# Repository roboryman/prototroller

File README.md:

## About
The Prototroller is a ***modular*** controller that is full-stack, feature-rich, responsive, and robust. The controller could be used for any HID-compliant purpose, but we focus on developing hot-swappable modules that can form customizable gamepads.

A potential use case is general hardware level remapping for quality of life. Another is rapidly prototyping different controller layouts for games or simulations in development.

Our team consists of 5 members:
- Yu-yang Hsieh
- Britton McLeavy
- Caleb O'Malley
- Merrick Ryman
- Evan Zhang

This project is developed in conjunction with the UF CpE Capstone program (Fall 2022 - Spring 2023). This project is self-funded. As such, donations are appreciated in this educational pursuit (hardware is not cheap nowadays).

## Architecture and Aesthetics
At the highest abstraction the Prototroller consists of the following:
- Master Board 
- Module Boards
- Component Interfaces
- Enclosures
- Firmware

### Master Board

<p>

The master board handles the data store of connected modules, transfers and receives data with modules over SPI, transfers and receives HID data over USB with the host, rescans modules, has buttons for various functions, etc. Most of the master board also serves as the the 4x5 grid of module slots the user can snap modules to using magnetic pogo-pin connectors.

<br clear="left"/>
</p>

The master board has buttons for rescanning, resetting, and flashing. There are header pins for interfacing with haptic feedback motors. A 3-pin JST-SH header (1.00mm) is available for serial wire debug. There is a USB-C receptacle (2.0) for power and data connection with the host.

The connection interface between the master board and module boards uses 6-pin magnetic pogo-pin connectors. These carry VCC, GND, and SPI signals, while maintaining a solid physical connection. The master board feeds modules with 3.3V.

### Module Boards

<p>

Module boards are generic and constrained at 30x30mm with no direct user interface (except for the connector and SWD headers). On the sides are headers providing 14 signals to a component interface board that would sit above. This way there are no unique module boards for each component, and we simply offload the task to the component interface board by hand.
<br clear="right"/>
</p>

### Component Interface Boards

<p>

The component interface boards are veroboards sitting above the module board headers. We may freely route signals from the module board to a component, the direct user interface.
<br clear="left"/>
</p>

### Enclosures

This would not be a very comfortable controller to use without enclosures.

The master board is enclosed by a chassis and grips. The master board is screwed to the chassis.

The module enclosures contain the module board and component interface boards, but do not cover the component.

### Firmware

Each type of module has its own assosciated firmware that can be flashed via the SWD header pins with picoprobe firmware. The master board can be flashed via the normal way of "dragging" the binaries. See below for more details on flashing. The Prototroller has been extensively tested on Windows systems, but will likely work on Mac, Linux, and generally any OS that supports HID gamepads.

## Usage
There are a few ways you may use the Prototroller.
### _Our Hardware, Our Software_
Recommended. This combines our hardware listed above with the firmware to do the job.
The end result is a full-stack modular controller.

Our recommended PCB supplier is JLCPCB, and we are working on formalizing our recommendations for ordering.

### _Your Hardware, Our Software_
If you want to develop your own hardware to use with our software, that is excellent! In fact, we are curious to see your designs.

You may use our designs as a starting point. For example, you may want to make the modules slightly larger.

## Building and Flashing Master Boards
You may use the provided VSCode launch debug configuration and flash task. This requires a Picoprobe, OpenOCD, and Cortex Debug. Instructions are available in ```/ide```.
An easier way is to use the USB receptacle to mount and flash RP2040 binaries (.uf2), accessible by holding down BOOTSEL and performing a reset. **If you are using VSCode, you can simply edit settings.json for your SDK path, build the target, and proceed to step 5**. Otherwise, the process to generate the binary is as so:
1. Ensure you have the Pico SDK cloned somewhere, such as ```~/pico-sdk```.
2. Make and cd into a 'build' subdirectory, and export the Pico SDK path:
    ```
    $ cd prototroller
    $ mkdir build
    $ cd build
    $ export PICO_SDK_PATH=...
    ```
3. Generate the build targets:
    ```
    $ cmake -DPICO_BOARD=prototroller ..
    ```
4. Build all targets by running `make`. To build only host, master, or module targets, cd into the respective directory (generated by the cmake command above) and execute `make`. In this case, you can just `cd` into master and execute `make`.
5. This will generate the appropriate `.uf2` binaries, which can be flashed by dragging onto the mount.

## Building and Flashing Module Boards
The module boards do not have a USB receptacle. You must use SWD in conjunction with a debug probe. We recommend the official Raspberry Pi Debug Probe ($12), or a Pico flashed with the Picoprobe firmware.

Instructions are available in ```/ide```. This is how you might do it after setting up Picoprobe, OpenOCD, etc:
1. Follow the steps listed in "Building and Flashing Master Boards" to generate the binary for the module boards.
2. Connect SWDIO and SWCLK from debug probe to the SWD headers above the flash on the module board (labeled on rear silkscreen).
3. Connect a *common ground* between the Picoprobe and the module board.
4. Snap the module board to a powered master board (alternatively, supply 3V3 through the female header).
5. If you are using WSL, pass-through the Picoprobe in Powershell using ```usbipd```.
6. Use the '```Prototroller Flash```' task in VSCode, or execute the following command, where `joystick-module.elf` is the name of the ELF executable generated previously:
    ```
    sudo openocd -f interface/cmsis-dap.cfg -f target/rp2040.cfg -c "adapter speed 5000" -c "program build/module/joystick-module.elf verify reset exit"
    ```
If all went well, the module board should be flashed. You can safely remove the SWD wires and set the debug probe aside.

Documentation for the official Raspberry Pi Debug Probe:
https://www.raspberrypi.com/documentation/microcontrollers/debug-probe.html

Alternatively, here is an excellent tutorial to setting up and using Picoprobe if you have a Pico available: https://github.com/robotdad/piconotes

## Roadmap
- [x] Proof of Concept Build
- [x] Basic Master/Module Firmware
- [x] Basic Host HID Drivers
- [x] Basic Component Support
- [x] Prototype Build
- [x] Interconnect Design
- [x] Module Board Design(s)
- [x] Master Board Design
- [x] Chassis/Module Enclosure Designs
- [x] Advanced Firmware
- [x] Advanced HID Drivers
- [x] Advanced Component Support
- [x] Finalized Firmware
- [x] Prototroller Artifact
- [ ] Stretch: Wireless Support
- [ ] Stretch: Power Optimization
- [ ] Stretch: More types of modules

Ideas for future modules: Trigger, D-Pad, Accelerometer, Gyroscope, Rounded Buttons. Could also do some cool things non-gaming related, such as an IR blaster and Bluetooth TX/RX modules.
Adding new types of modules only requires the firmware and custom backpack.

## Acknowledgements
Thank you to our stakeholder Carsten Thue-Bludworth for his infinite wisdom. His assistance keeps the project grounded and evolving in the best way possible.

Thank you to Dr. Blanchard and the UF CpE Capstone program for direction and usage of lab space.

Thank you to the Raspberry Pi community for the hardware and software that made this project possible.

Thank you to Phil's Lab on YouTube for the excellent courses and tutorials on hardware design.

Thank you to user testing participants for valuable feedback. Their insights and suggestions have helped us refine our design and ensure that our final product meets the needs and expectations of its intended users.

Thank you to families, friends, and loved ones for their unwavering support and encouragement. Their belief in our abilities and commitment to our success has been a constant source of motivation and inspiration.

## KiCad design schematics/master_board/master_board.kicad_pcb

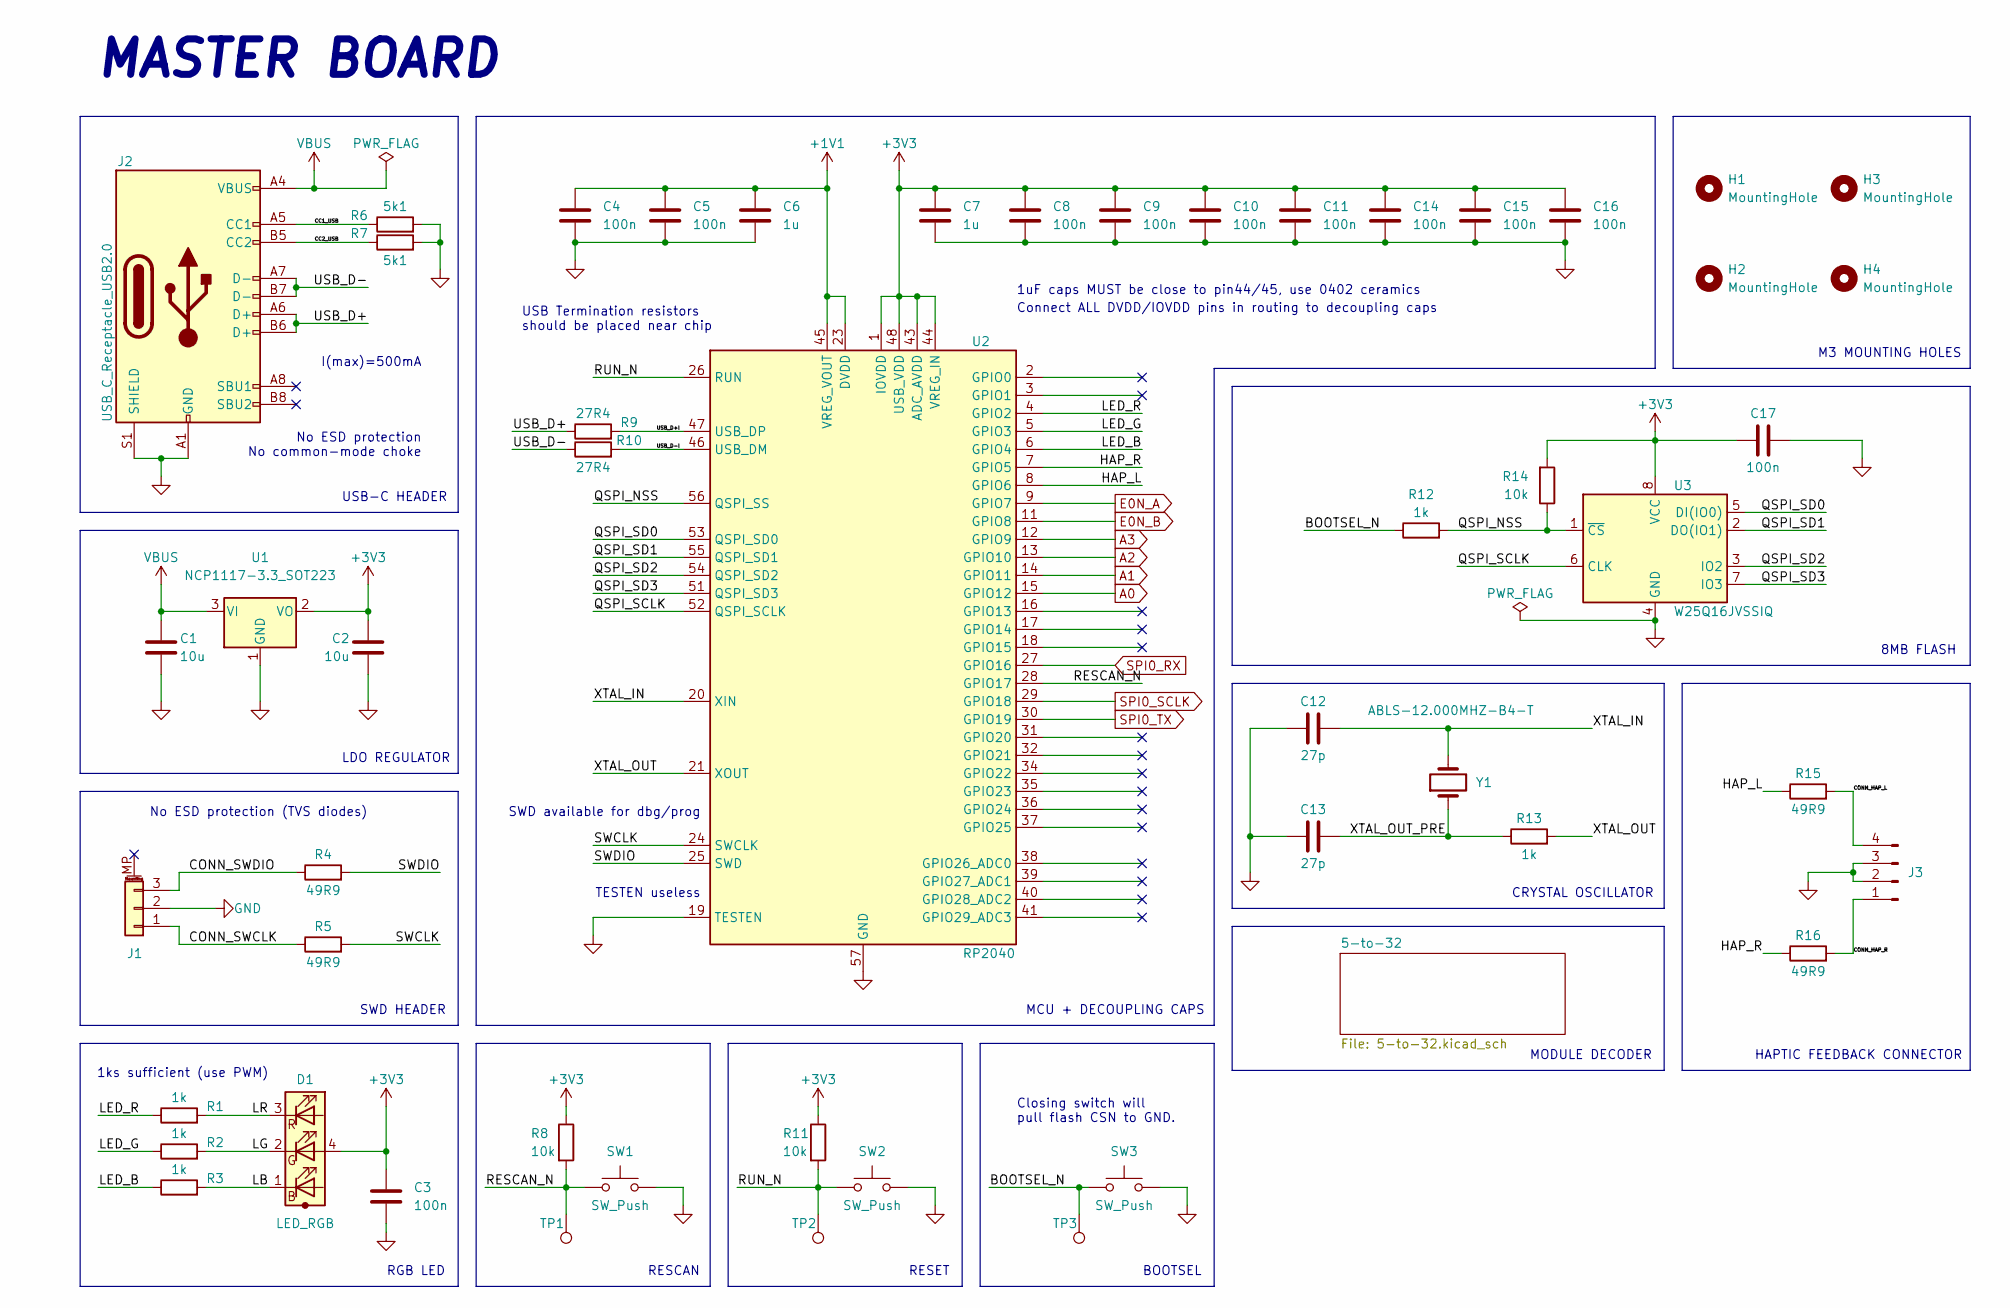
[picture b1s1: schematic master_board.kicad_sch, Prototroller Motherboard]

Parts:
C1, C2: 10u; C_0805_2012Metric; Manufacturer Part Number CL21A106KOQNNNG
C3, C4, C5, C8, C9, C10, C11, C14, C15, C16, C17: 100n; C_0402_1005Metric; Manufacturer Part Number C0402X7R100-104KNE-CT
C6, C7: 1u; C_0402_1005Metric; Manufacturer Part Number C0402X5R6R3-105KNP-CT
C12, C13: 27p; C_0402_1005Metric; Manufacturer Part Number C0402C0G250-270JNE-CT
D1: LED_RGB; LED_Cree-UHD111A; Manufacturer Part Number UHD111A-FKA-C3K23E1L3VG5ZB3Z3
H1, H2, H3, H4: MountingHole; MountingHole_3.2mm_M3
J1: Conn_01x03_MountingPin; JST_SH_BM03B-SRSS-TB_1x03-1MP_P1.00mm_Vertical
J2: USB_C_Receptacle_USB2.0; USB_C_Receptacle_GCT_USB4105-xx-A_16P_TopMnt_Horizontal; Manufacturer Part Number USB4105-GF-A
J3: Conn_01x04_Male; PinHeader_1x04_P2.54mm_Vertical
R1, R2, R3, R13: 1k; R_0402_1005Metric; Manufacturer Part Number RC0402FR-7W1KL
R4, R5: 49R9; R_0402_1005Metric; Manufacturer Part Number RC0402FR-7W49R9L
R6, R7: 5k1; R_0402_1005Metric; Manufacturer Part Number ERJ-2RKF5101X
R8, R11, R14: 10k; R_0402_1005Metric; Manufacturer Part Number RC0402JR-7W10KL
R9, R10: 27R4; R_0402_1005Metric; Manufacturer Part Number CRGP0402F27R
R12: 1k; R_0402_1005Metric; Manufacturer Part Number RC0402JR-7W10KL
R15, R16: 49R9; R_0402_1005Metric; Manufacturer Part Number RC0402FR-7W1KL
SW1, SW2, SW3: SW_Push; Switch_D6C40F1LFS; Manufacturer Part Number D6C40 F1 LFS
TP1, TP2, TP3: TestPoint; TestPoint_Pad_2.5x2.5mm
U1: NCP1117-3.3_SOT223; SOT-223-3_TabPin2; Manufacturer Part Number NCP1117LPST33T3G
U2: RP2040; QFN-56-1EP_7x7mm_P0.4mm_EP3.2x3.2mm; Manufacturer Part Number SC0914(13)
U3: W25Q16JVSSIQ; SOIC-8_5.23x5.23mm_P1.27mm; Manufacturer Part Number W25Q16JVSSIQ
Y1: ABLS-12.000MHZ-B4-T; XTAL_ABLS-12.000MHZ-B4-T; Manufacturer Part Number ABLS-12.000MHZ-B4-T

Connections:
+1V1: C4.1, C5.1, C6.1, U2.23 (DVDD), U2.45 (VREG_VOUT), U2.50 (DVDD)
+3V3: C2.2, C3.1, C7.1, C8.1, C9.1, C10.1, C11.1, C14.1, C15.1, C16.1, C17.1, D1.4 (A), R8.1, R11.1, R14.2, U1.2 (VO), U2.1 (IOVDD), U2.10 (IOVDD), U2.22 (IOVDD), U2.33 (IOVDD), U2.42 (IOVDD), U2.43 (ADC_AVDD), U2.44 (VREG_IN), U2.48 (USB_VDD), U2.49 (IOVDD), U3.8 (VCC); also elsewhere on the board
/BOOTSEL_N: R12.1, SW3.1, TP3.1
/CC1_USB: J2.A5 (CC1), R6.1
/CC2_USB: J2.B5 (CC2), R7.1
/CONN_HAP_L: J3.4, R15.2
/CONN_HAP_R: J3.1, R16.2
/CONN_SWCLK: J1.1, R5.1
/CONN_SWDIO: J1.3, R4.1
/HAP_L: R15.1, U2.8 (GPIO6)
/HAP_R: R16.1, U2.7 (GPIO5)
/LB: D1.1 (B), R3.2
/LED_B: R3.1, U2.6 (GPIO4)
/LED_G: R2.1, U2.5 (GPIO3)
/LED_R: R1.1, U2.4 (GPIO2)
/LG: D1.2 (G), R2.2
/LR: D1.3 (R), R1.2
/QSPI_NSS: R12.2, R14.1, U2.56 (QSPI_SS), U3.1 (~CS)
/QSPI_SCLK: U2.52 (QSPI_SCLK), U3.6 (CLK)
/QSPI_SD0: U2.53 (QSPI_SD0), U3.5 (DI(IO0))
/QSPI_SD1: U2.55 (QSPI_SD1), U3.2 (DO(IO1))
/QSPI_SD2: U2.54 (QSPI_SD2), U3.3 (IO2)
/QSPI_SD3: U2.51 (QSPI_SD3), U3.7 (IO3)
/RESCAN_N: R8.2, SW1.1, TP1.1, U2.28 (GPIO17)
/RUN_N: R11.2, SW2.1, TP2.1, U2.26 (RUN)
/SWCLK: R5.2, U2.24 (SWCLK)
/SWDIO: R4.2, U2.25 (SWD)
/USB_D+: J2.A6 (D+), J2.B6 (D+), R9.1
/USB_D+I: R9.2, U2.47 (USB_DP)
/USB_D-: J2.A7 (D-), J2.B7 (D-), R10.1
/USB_D-I: R10.2, U2.46 (USB_DM)
/XTAL_IN: C12.2, U2.20 (XIN), Y1.2
/XTAL_OUT: R13.2, U2.21 (XOUT)
/XTAL_OUT_PRE: C13.2, R13.1, Y1.1
A0: U2.15 (GPIO12); also elsewhere on the board
A1: U2.14 (GPIO11); also elsewhere on the board
A2: U2.13 (GPIO10); also elsewhere on the board
A3: U2.12 (GPIO9); also elsewhere on the board
E0N_A: U2.9 (GPIO7); also elsewhere on the board
E0N_B: U2.11 (GPIO8); also elsewhere on the board
GND: C1.2, C2.1, C3.2, C4.2, C5.2, C6.2, C7.2, C8.2, C9.2, C10.2, C11.2, C12.1, C13.1, C14.2, C15.2, C16.2, C17.2, J1.2, J2.A1 (GND), J2.A12 (GND), J2.B1 (GND), J2.B12 (GND), J2.S1 (SHIELD), J3.2, J3.3, R6.2, R7.2, SW1.2, SW2.2, SW3.2, U1.1 (GND), U2.19 (TESTEN), U2.57 (GND), U3.4 (GND); also elsewhere on the board
SPI0_RX: U2.27 (GPIO16); also elsewhere on the board
SPI0_SCLK: U2.29 (GPIO18); also elsewhere on the board
SPI0_TX: U2.30 (GPIO19); also elsewhere on the board
VBUS: C1.1, J2.A4 (VBUS), J2.A9 (VBUS), J2.B4 (VBUS), J2.B9 (VBUS), U1.3 (VI)

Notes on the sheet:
RESET
MODULE DECODER
SWD HEADER
1ks sufficient (use PWM)
USB-C HEADER
M3 MOUNTING HOLES
CRYSTAL OSCILLATOR
RGB LED
1uF caps MUST be close to pin44/45, use 0402 ceramics
USB Termination resistors should be placed near chip
TESTEN useless
HAPTIC FEEDBACK CONNECTOR
RESCAN
LDO REGULATOR
Connect ALL DVDD/IOVDD pins in routing to decoupling caps
No ESD protection No common-mode choke
SWD available for dbg/prog
BOOTSEL
8MB FLASH
Closing switch will pull flash CSN to GND.
I(max)=500mA
No ESD protection (TVS diodes)
MCU + DECOUPLING CAPS
MASTER BOARD

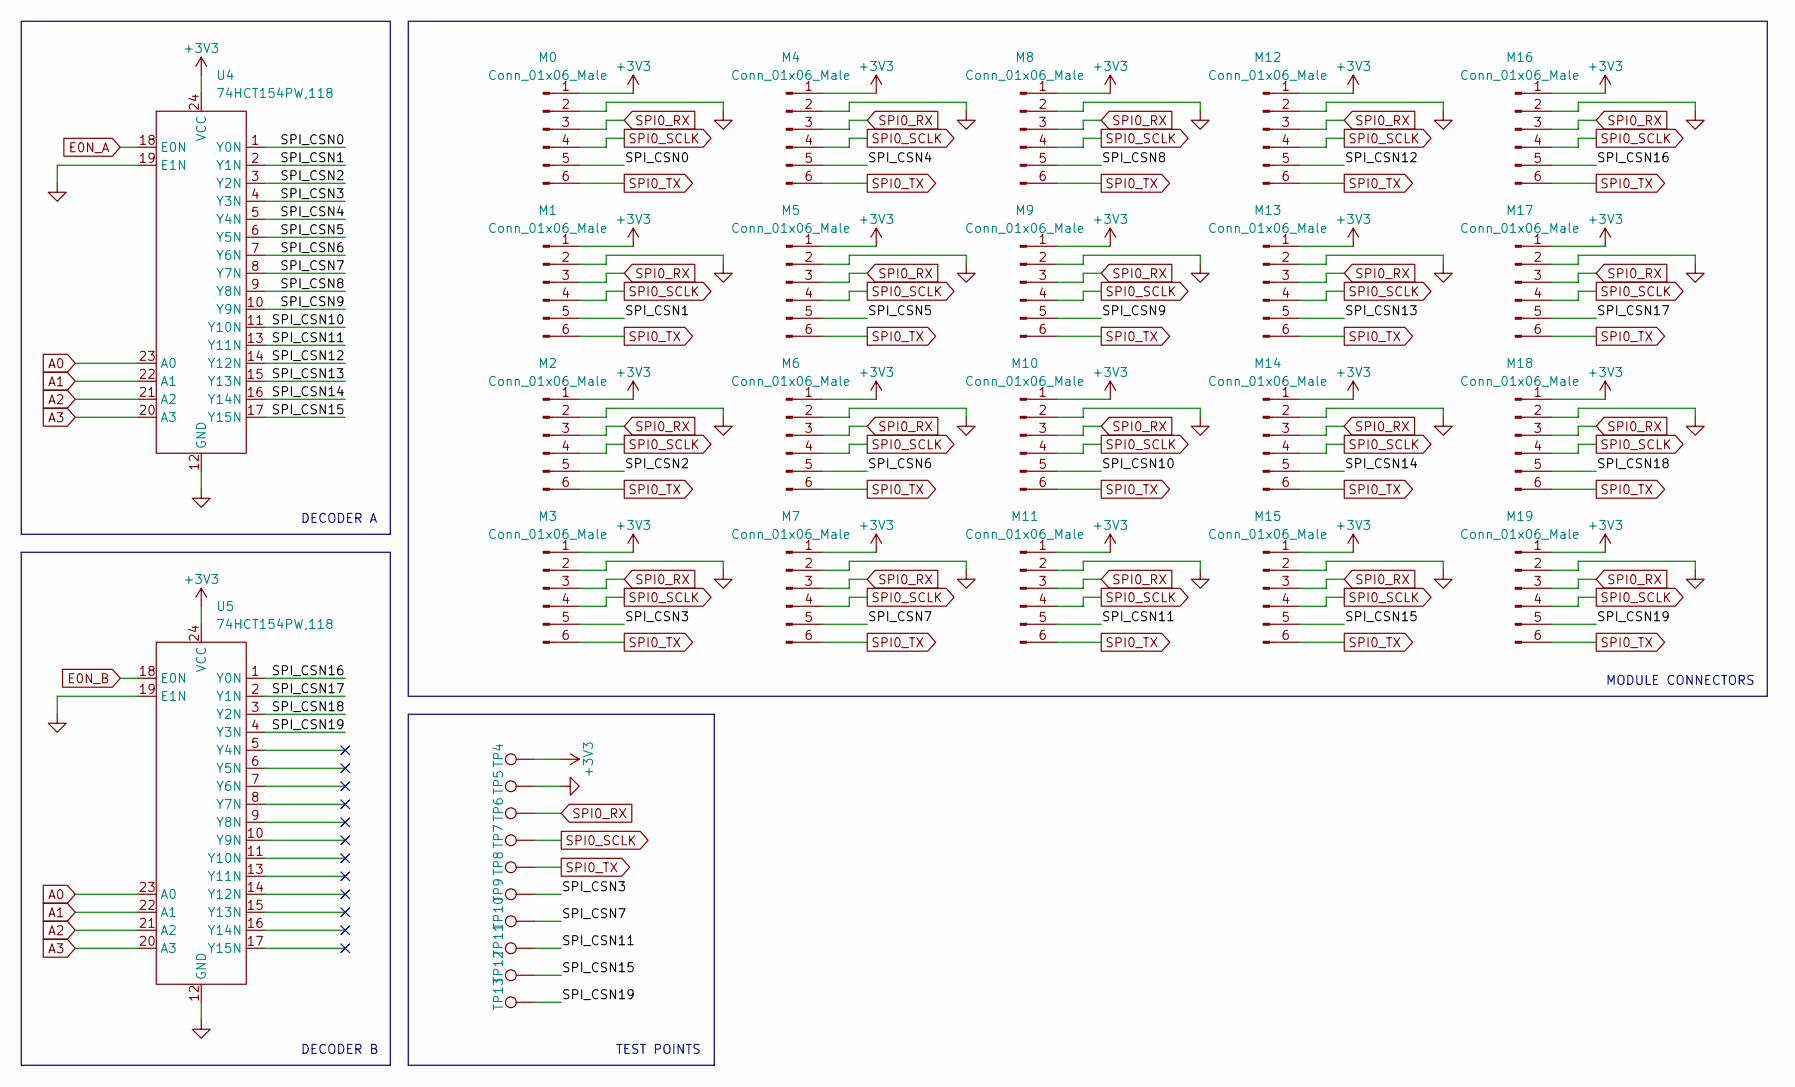
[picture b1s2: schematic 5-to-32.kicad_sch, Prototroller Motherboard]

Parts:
M0, M1, M2, M3, M4, M5, M6, M7, M8, M9, M10, M11, M12, M13, M14, M15, M16, M17, M18, M19: Conn_01x06_Male; Mag_Pogo_6P_P2.2mm_Female
TP4, TP5, TP6, TP7, TP8, TP9, TP10, TP11, TP12, TP13: TestPoint; TestPoint_Pad_2.5x2.5mm
U4, U5: 74HCT154PW,118; TSSOP-24_4.4x7.8mm_P0.65mm; Manufacturer Part Number 74HCT154PW,118

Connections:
+3V3: M0.1, M1.1, M2.1, M3.1, M4.1, M5.1, M6.1, M7.1, M8.1, M9.1, M10.1, M11.1, M12.1, M13.1, M14.1, M15.1, M16.1, M17.1, M18.1, M19.1, TP4.1, U4.24 (VCC), U5.24 (VCC); also elsewhere on the board
/5-to-32/SPI_CSN0: M0.5, U4.1 (Y0N)
/5-to-32/SPI_CSN1: M1.5, U4.2 (Y1N)
/5-to-32/SPI_CSN2: M2.5, U4.3 (Y2N)
/5-to-32/SPI_CSN3: M3.5, TP9.1, U4.4 (Y3N)
/5-to-32/SPI_CSN4: M4.5, U4.5 (Y4N)
/5-to-32/SPI_CSN5: M5.5, U4.6 (Y5N)
/5-to-32/SPI_CSN6: M6.5, U4.7 (Y6N)
/5-to-32/SPI_CSN7: M7.5, TP10.1, U4.8 (Y7N)
/5-to-32/SPI_CSN8: M8.5, U4.9 (Y8N)
/5-to-32/SPI_CSN9: M9.5, U4.10 (Y9N)
/5-to-32/SPI_CSN10: M10.5, U4.11 (Y10N)
/5-to-32/SPI_CSN11: M11.5, TP11.1, U4.13 (Y11N)
/5-to-32/SPI_CSN12: M12.5, U4.14 (Y12N)
/5-to-32/SPI_CSN13: M13.5, U4.15 (Y13N)
/5-to-32/SPI_CSN14: M14.5, U4.16 (Y14N)
/5-to-32/SPI_CSN15: M15.5, TP12.1, U4.17 (Y15N)
/5-to-32/SPI_CSN16: M16.5, U5.1 (Y0N)
/5-to-32/SPI_CSN17: M17.5, U5.2 (Y1N)
/5-to-32/SPI_CSN18: M18.5, U5.3 (Y2N)
/5-to-32/SPI_CSN19: M19.5, TP13.1, U5.4 (Y3N)
A0: U4.23 (A0), U5.23 (A0); also elsewhere on the board
A1: U4.22 (A1), U5.22 (A1); also elsewhere on the board
A2: U4.21 (A2), U5.21 (A2); also elsewhere on the board
A3: U4.20 (A3), U5.20 (A3); also elsewhere on the board
E0N_A: U4.18 (E0N); also elsewhere on the board
E0N_B: U5.18 (E0N); also elsewhere on the board
GND: M0.2, M1.2, M2.2, M3.2, M4.2, M5.2, M6.2, M7.2, M8.2, M9.2, M10.2, M11.2, M12.2, M13.2, M14.2, M15.2, M16.2, M17.2, M18.2, M19.2, TP5.1, U4.12 (GND), U4.19 (E1N), U5.12 (GND), U5.19 (E1N); also elsewhere on the board
SPI0_RX: M0.3, M1.3, M2.3, M3.3, M4.3, M5.3, M6.3, M7.3, M8.3, M9.3, M10.3, M11.3, M12.3, M13.3, M14.3, M15.3, M16.3, M17.3, M18.3, M19.3, TP6.1; also elsewhere on the board
SPI0_SCLK: M0.4, M1.4, M2.4, M3.4, M4.4, M5.4, M6.4, M7.4, M8.4, M9.4, M10.4, M11.4, M12.4, M13.4, M14.4, M15.4, M16.4, M17.4, M18.4, M19.4, TP7.1; also elsewhere on the board
SPI0_TX: M0.6, M1.6, M2.6, M3.6, M4.6, M5.6, M6.6, M7.6, M8.6, M9.6, M10.6, M11.6, M12.6, M13.6, M14.6, M15.6, M16.6, M17.6, M18.6, M19.6, TP8.1; also elsewhere on the board

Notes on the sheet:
MODULE CONNECTORS
DECODER B
DECODER A
TEST POINTS

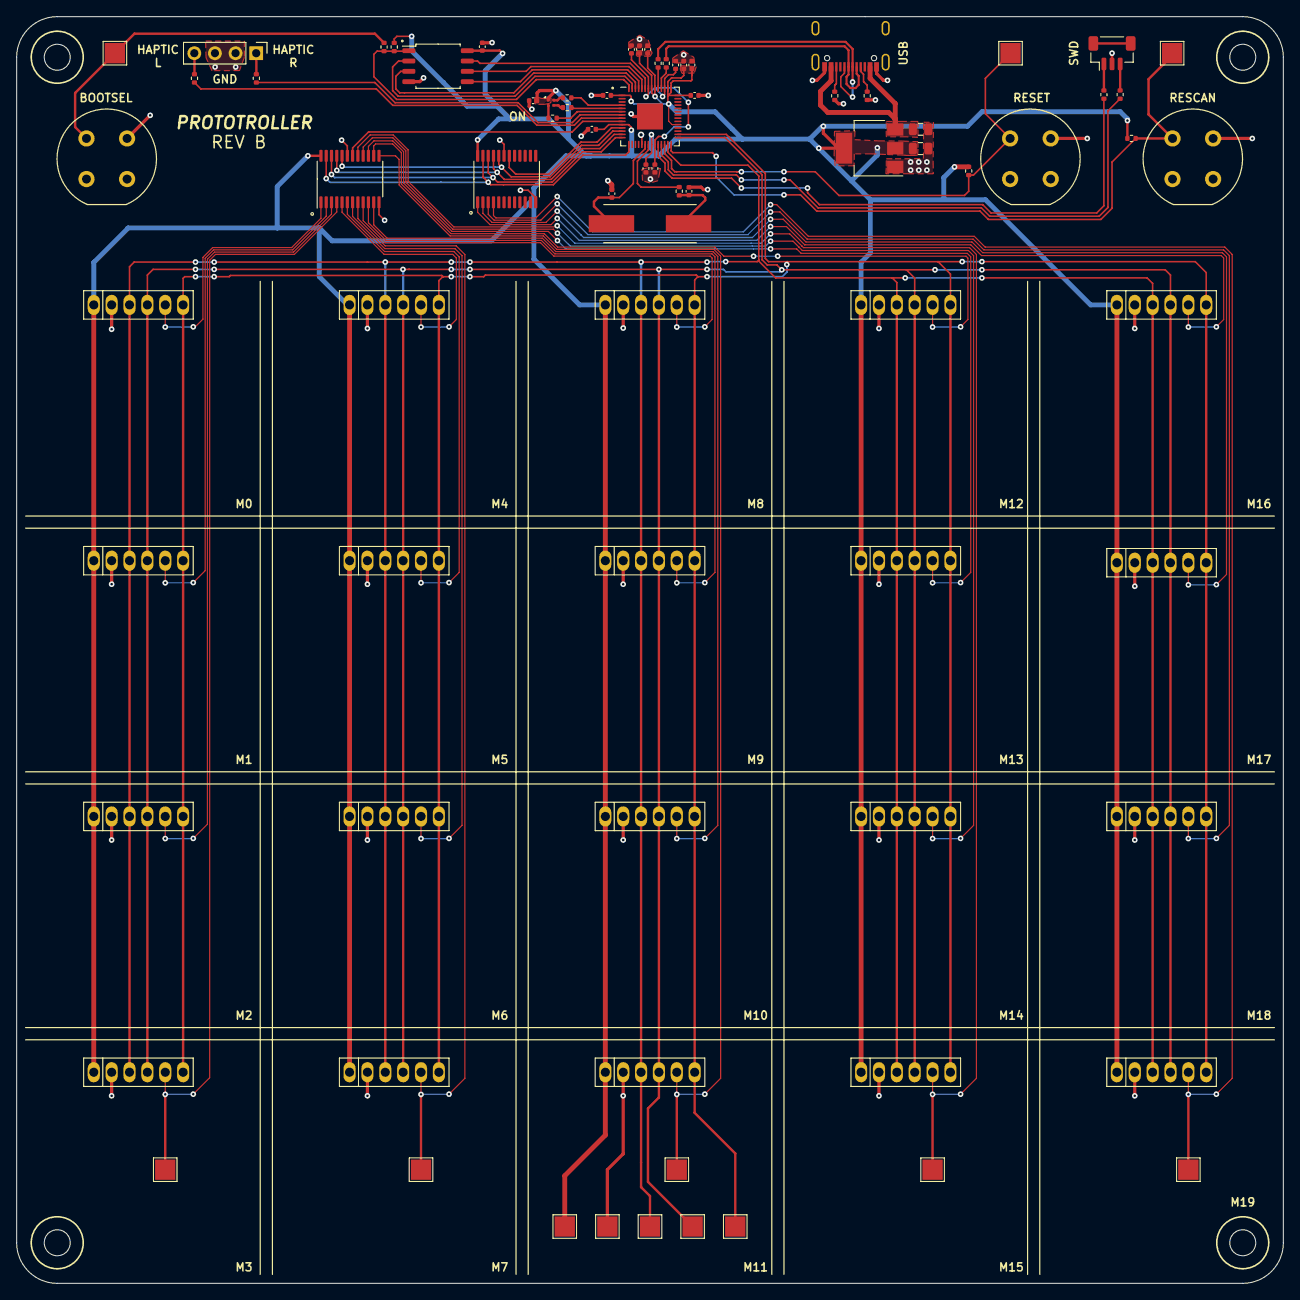
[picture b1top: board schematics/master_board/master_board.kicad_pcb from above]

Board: 2 copper layers, 156.0 x 156.0 mm, 83 parts (0 on the bottom side), 65 nets.

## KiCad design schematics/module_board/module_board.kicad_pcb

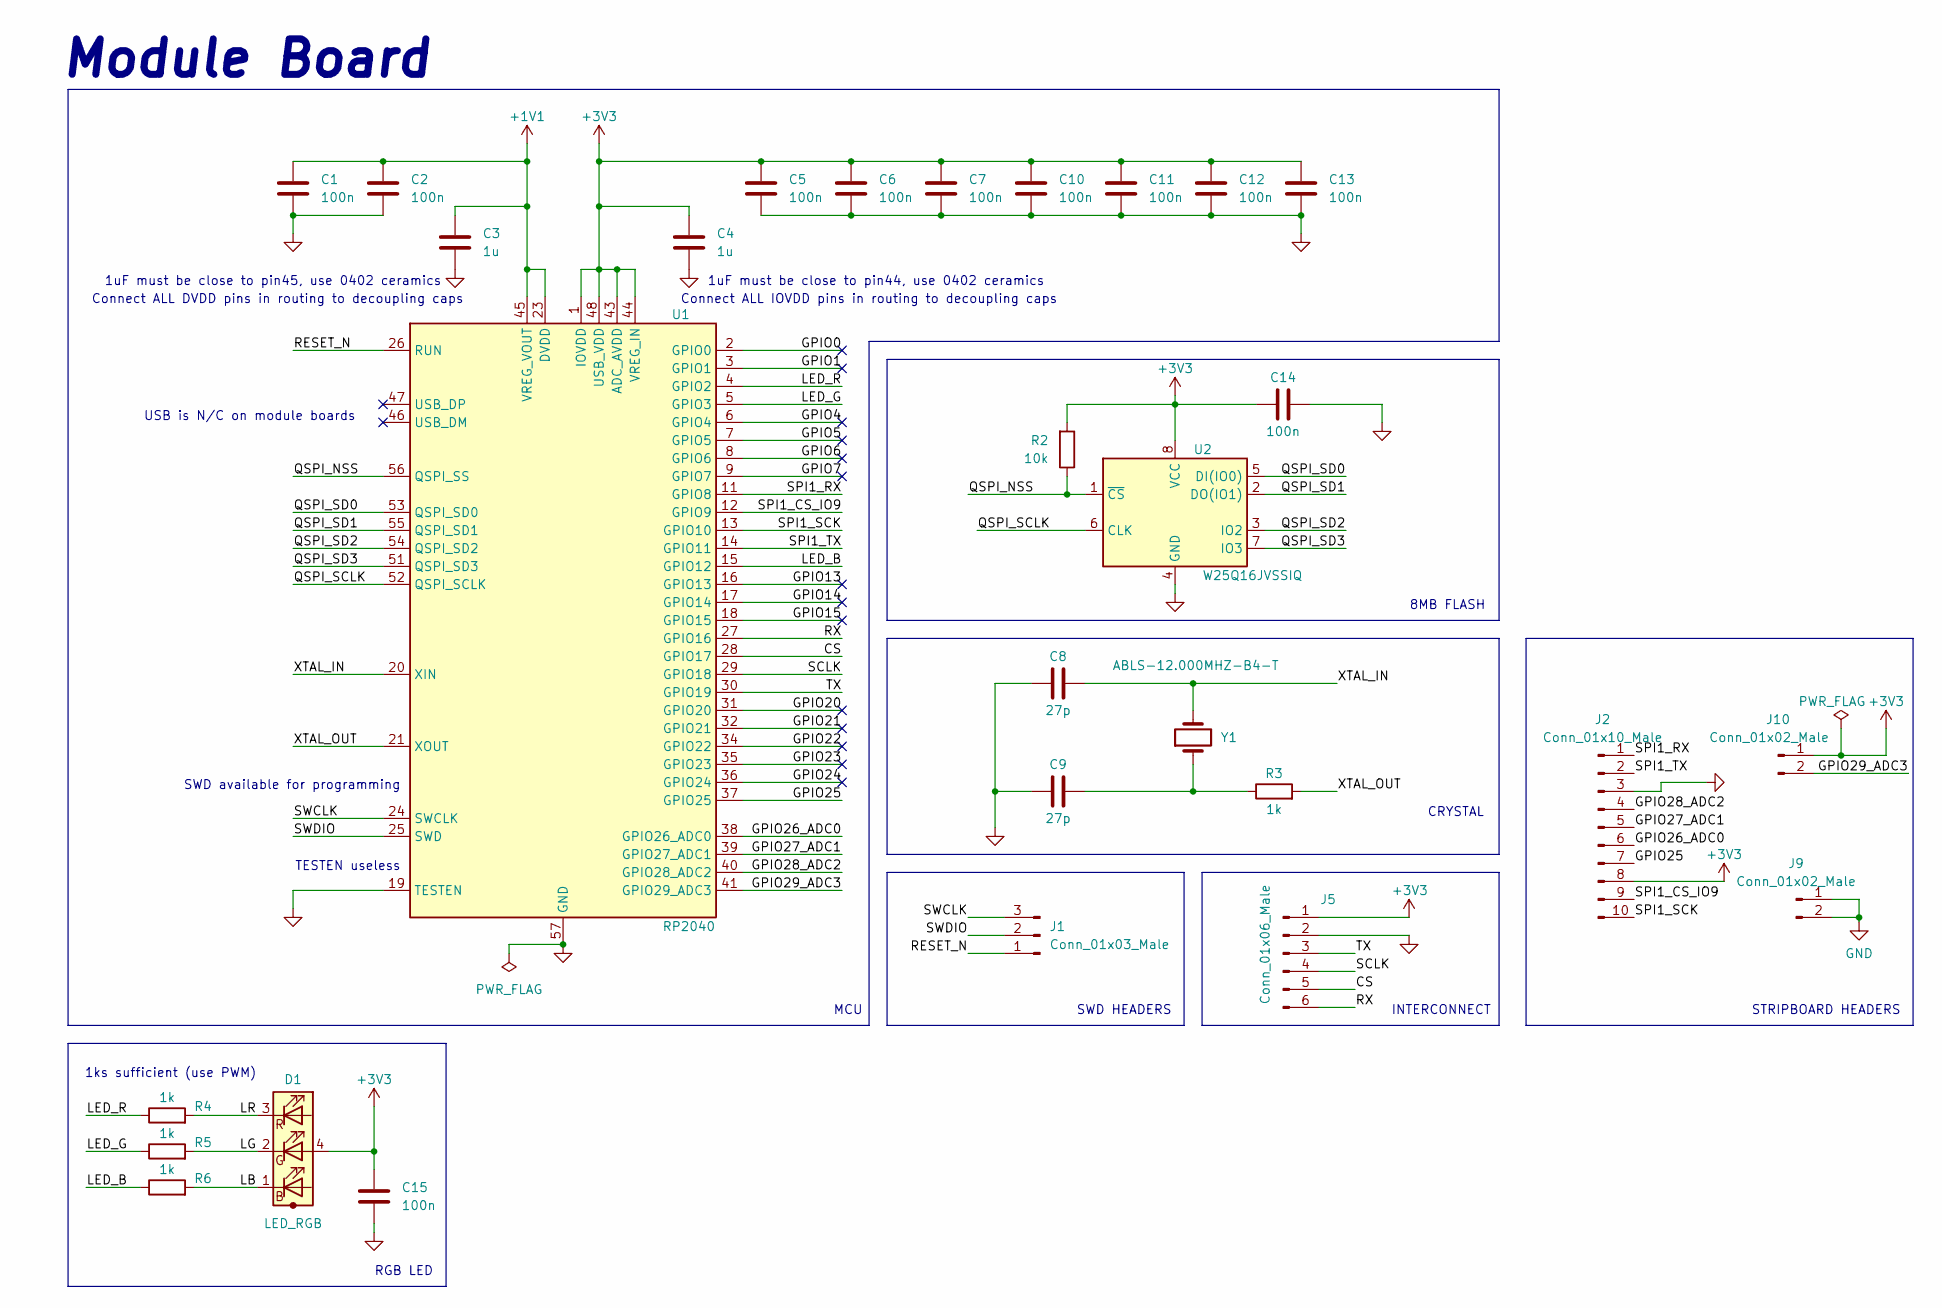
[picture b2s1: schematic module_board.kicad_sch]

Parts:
C1, C2, C5, C6, C7, C10, C11, C12, C13, C14: 100n; C_0402_1005Metric
C3, C4: 1u; C_0402_1005Metric
C8, C9: 27p; C_0402_1005Metric
C15: 100n; C_0402_1005Metric; Manufacturer Part Number C0402X7R100-104KNE-CT
D1: LED_RGB; LED_Cree-UHD111A; Manufacturer Part Number UHD111A-FKA-C3K23E1L3VG5ZB3Z3
J1: Conn_01x03_Male; PinHeader_1x03_P2.54mm_Vertical
J2: Conn_01x10_Male; PinHeader_1x10_P2.54mm_Vertical
J5: Conn_01x06_Male; Mag_Pogo_6P_P2.2mm_Male
J9, J10: Conn_01x02_Male; PinHeader_1x02_P2.54mm_Vertical
R2: 10k; R_0402_1005Metric
R3: 1k; R_0402_1005Metric
R4, R5, R6: 1k; R_0402_1005Metric; Manufacturer Part Number RC0402FR-7W1KL
U1: RP2040; QFN-56-1EP_7x7mm_P0.4mm_EP3.2x3.2mm
U2: W25Q16JVSSIQ; SOIC-8_5.23x5.23mm_P1.27mm
Y1: ABLS-12.000MHZ-B4-T; XTAL_ABLS-12.000MHZ-B4-T

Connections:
+1V1: C1.1, C2.1, C3.2, U1.23 (DVDD), U1.45 (VREG_VOUT), U1.50 (DVDD)
+3V3: C4.1, C5.1, C6.1, C7.1, C10.1, C11.1, C12.1, C13.1, C14.1, C15.1, D1.4 (A), J2.8, J5.1, J10.1, R2.2, U1.1 (IOVDD), U1.10 (IOVDD), U1.22 (IOVDD), U1.33 (IOVDD), U1.42 (IOVDD), U1.43 (ADC_AVDD), U1.44 (VREG_IN), U1.48 (USB_VDD), U1.49 (IOVDD), U2.8 (VCC)
/CS: J5.5, U1.28 (GPIO17)
/GPIO0: U1.2 (GPIO0)
/GPIO1: U1.3 (GPIO1)
/GPIO4: U1.6 (GPIO4)
/GPIO5: U1.7 (GPIO5)
/GPIO6: U1.8 (GPIO6)
/GPIO7: U1.9 (GPIO7)
/GPIO13: U1.16 (GPIO13)
/GPIO14: U1.17 (GPIO14)
/GPIO15: U1.18 (GPIO15)
/GPIO20: U1.31 (GPIO20)
/GPIO21: U1.32 (GPIO21)
/GPIO22: U1.34 (GPIO22)
/GPIO23: U1.35 (GPIO23)
/GPIO24: U1.36 (GPIO24)
/GPIO25: J2.7, U1.37 (GPIO25)
/GPIO26_ADC0: J2.6, U1.38 (GPIO26_ADC0)
/GPIO27_ADC1: J2.5, U1.39 (GPIO27_ADC1)
/GPIO28_ADC2: J2.4, U1.40 (GPIO28_ADC2)
/GPIO29_ADC3: J10.2, U1.41 (GPIO29_ADC3)
/LB: D1.1 (B), R6.2
/LED_B: R6.1, U1.15 (GPIO12)
/LED_G: R5.1, U1.5 (GPIO3)
/LED_R: R4.1, U1.4 (GPIO2)
/LG: D1.2 (G), R5.2
/LR: D1.3 (R), R4.2
/QSPI_NSS: R2.1, U1.56 (QSPI_SS), U2.1 (~CS)
/QSPI_SCLK: U1.52 (QSPI_SCLK), U2.6 (CLK)
/QSPI_SD0: U1.53 (QSPI_SD0), U2.5 (DI(IO0))
/QSPI_SD1: U1.55 (QSPI_SD1), U2.2 (DO(IO1))
/QSPI_SD2: U1.54 (QSPI_SD2), U2.3 (IO2)
/QSPI_SD3: U1.51 (QSPI_SD3), U2.7 (IO3)
/RESET_N: J1.1, U1.26 (RUN)
/RX: J5.6, U1.27 (GPIO16)
/SCLK: J5.4, U1.29 (GPIO18)
/SPI1_CS_IO9: J2.9, U1.12 (GPIO9)
/SPI1_RX: J2.1, U1.11 (GPIO8)
/SPI1_SCK: J2.10, U1.13 (GPIO10)
/SPI1_TX: J2.2, U1.14 (GPIO11)
/SWCLK: J1.3, U1.24 (SWCLK)
/SWDIO: J1.2, U1.25 (SWD)
/TX: J5.3, U1.30 (GPIO19)
/XTAL_IN: C8.2, U1.20 (XIN), Y1.2
/XTAL_OUT: R3.2, U1.21 (XOUT)
GND: C1.2, C2.2, C3.1, C4.2, C5.2, C6.2, C7.2, C8.1, C9.1, C10.2, C11.2, C12.2, C13.2, C14.2, C15.2, J2.3, J5.2, J9.1, J9.2, U1.19 (TESTEN), U1.57 (GND), U2.4 (GND)
unnamed: C9.2, R3.1, Y1.1

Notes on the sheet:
SWD HEADERS
STRIPBOARD HEADERS
CRYSTAL
TESTEN useless
1uF must be close to pin44, use 0402 ceramics
MCU
RGB LED
8MB FLASH
USB is N/C on module boards
Module Board
1uF must be close to pin45, use 0402 ceramics
Connect ALL DVDD pins in routing to decoupling caps
1ks sufficient (use PWM)
INTERCONNECT
Connect ALL IOVDD pins in routing to decoupling caps
SWD available for programming

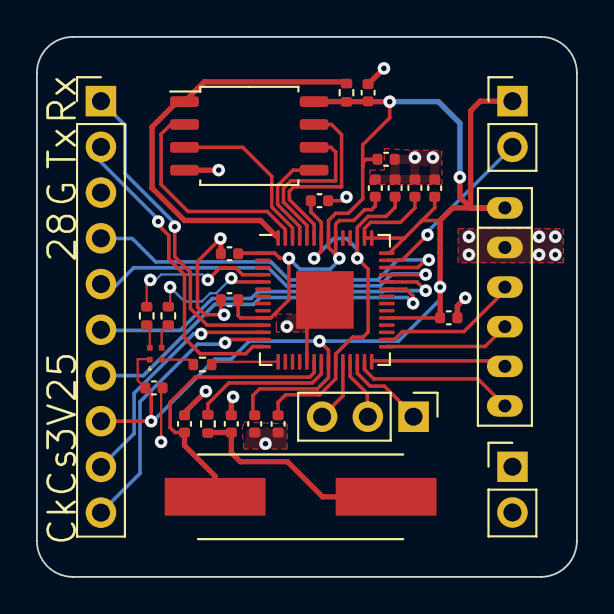
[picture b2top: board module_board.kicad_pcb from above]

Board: 2 copper layers, 30.0 x 30.0 mm, 29 parts (0 on the bottom side), 34 nets.

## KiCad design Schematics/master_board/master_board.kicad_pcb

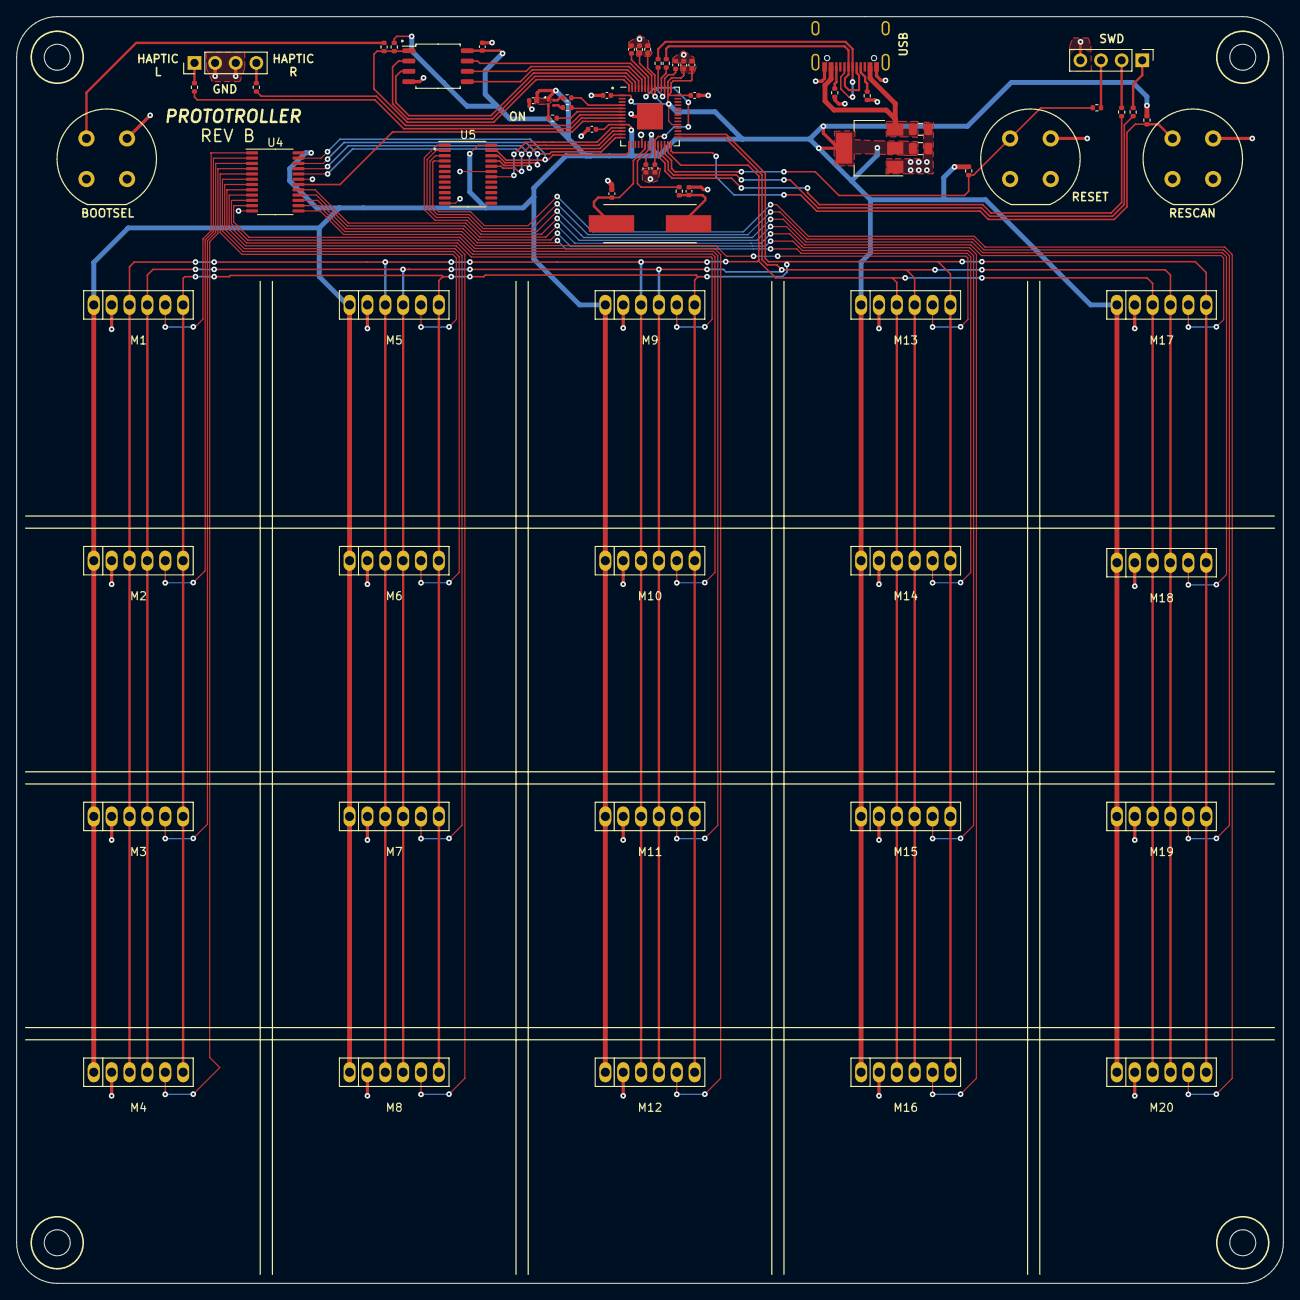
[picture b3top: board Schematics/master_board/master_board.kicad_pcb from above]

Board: 2 copper layers, 156.0 x 156.0 mm, 71 parts (0 on the bottom side), 66 nets.

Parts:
C1, C2: 10u; C_0805_2012Metric
C3, C4, C5, C8, C9, C10, C11, C14, C15, C16, C17: 100n; C_0402_1005Metric
C6, C7: 1u; C_0402_1005Metric
C12, C13: 27p; C_0402_1005Metric
D1: LED_RGB; LED_Cree-UHD111A
H1, H2, H3, H4: MountingHole; MountingHole_3.2mm_M3
J1: USB_C_Receptacle_USB2.0; USB_C_Receptacle_GCT_USB4105-xx-A_16P_TopMnt_Horizontal
J2: Conn_01x04_Male; PinHeader_1x04_P2.54mm_Vertical
J3: Conn_01x04_Female; PinHeader_1x04_P2.54mm_Vertical
M1, M2, M3, M4, M5, M6, M7, M8, M9, M10, M11, M12, M13, M14, M15, M16, M17, M18, M19, M20: Conn_01x06_Male; Mag_Pogo_6P_P2.2mm_Female
R1, R2, R3, R9, R12, R13, R14, R16, R17: 1k; R_0402_1005Metric
R4, R5, R6: 49R9; R_0402_1005Metric
R7, R8: 5k1; R_0402_1005Metric
R10, R11: 27R4; R_0402_1005Metric
R15: DNF; R_0402_1005Metric
SW1, SW2, SW3: SW_Push; Switch_D6C40F1LFS
U1: NCP1117-3.3_SOT223; SOT-223-3_TabPin2
U2: RP2040; QFN-56-1EP_7x7mm_P0.4mm_EP3.2x3.2mm
U3: W25Q16JVSSIQ; SOIC-8_5.23x5.23mm_P1.27mm
U4, U5: 74HCT154PW,118; TSSOP-24_4.4x7.8mm_P0.65mm
Y1: ABLS-12.000MHZ-B4-T; XTAL_ABLS-12.000MHZ-B4-T

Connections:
+1V1: C4.1, C5.1, C6.1, U2.23 (DVDD), U2.45 (VREG_VOUT), U2.50 (DVDD)
+3V3: C2.2, C3.1, C7.1, C8.1, C9.1, C10.1, C11.1, C14.1, C15.1, C16.1, C17.1, D1.4 (A), M1.1, M2.1, M3.1, M4.1, M5.1, M6.1, M7.1, M8.1, M9.1, M10.1, M11.1, M12.1, M13.1, M14.1, M15.1, M16.1, M17.1, M18.1, M19.1, M20.1, R9.1, R12.1, R15.2, U1.2 (VO), U2.1 (IOVDD), U2.10 (IOVDD), U2.22 (IOVDD), U2.33 (IOVDD), U2.42 (IOVDD), U2.43 (ADC_AVDD), U2.44 (VREG_IN), U2.48 (USB_VDD), U2.49 (IOVDD), U3.8 (VCC), U4.24 (VCC), U5.24 (VCC)
/5-to-32/SPI_CSN0: M1.5, U4.1 (Y0N)
/5-to-32/SPI_CSN1: M2.5, U4.2 (Y1N)
/5-to-32/SPI_CSN2: M3.5, U4.3 (Y2N)
/5-to-32/SPI_CSN3: M4.5, U4.4 (Y3N)
/5-to-32/SPI_CSN4: M5.5, U4.5 (Y4N)
/5-to-32/SPI_CSN5: M6.5, U4.6 (Y5N)
/5-to-32/SPI_CSN6: M7.5, U4.7 (Y6N)
/5-to-32/SPI_CSN7: M8.5, U4.8 (Y7N)
/5-to-32/SPI_CSN8: M9.5, U4.9 (Y8N)
/5-to-32/SPI_CSN9: M10.5, U4.10 (Y9N)
/5-to-32/SPI_CSN10: M11.5, U4.11 (Y10N)
/5-to-32/SPI_CSN11: M12.5, U4.13 (Y11N)
/5-to-32/SPI_CSN12: M13.5, U4.14 (Y12N)
/5-to-32/SPI_CSN13: M14.5, U4.15 (Y13N)
/5-to-32/SPI_CSN14: M15.5, U4.16 (Y14N)
/5-to-32/SPI_CSN15: M16.5, U4.17 (Y15N)
/5-to-32/SPI_CSN16: M17.5, U5.1 (Y0N)
/5-to-32/SPI_CSN17: M18.5, U5.2 (Y1N)
/5-to-32/SPI_CSN18: M19.5, U5.3 (Y2N)
/5-to-32/SPI_CSN19: M20.5, U5.4 (Y3N)
/BOOTSEL_N: R13.1, SW3.1
/CC1_USB: J1.A5 (CC1), R7.1
/CC2_USB: J1.B5 (CC2), R8.1
/CONN_HAP_L: J3.1, R16.2
/CONN_HAP_R: J3.4, R17.2
/CONN_RUN_N: J2.3, R6.1
/CONN_SWCLK: J2.2, R5.1
/CONN_SWDIO: J2.1, R4.1
/HAP_L: R16.1, U2.8 (GPIO6)
/HAP_R: R17.1, U2.7 (GPIO5)
/LB: D1.1 (B), R3.2
/LED_B: R3.1, U2.6 (GPIO4)
/LED_G: R2.1, U2.5 (GPIO3)
/LED_R: R1.1, U2.4 (GPIO2)
/LG: D1.2 (G), R2.2
/LR: D1.3 (R), R1.2
/QSPI_NSS: R13.2, R15.1, U2.56 (QSPI_SS), U3.1 (~CS)
/QSPI_SCLK: U2.52 (QSPI_SCLK), U3.6 (CLK)
/QSPI_SD0: U2.53 (QSPI_SD0), U3.5 (DI(IO0))
/QSPI_SD1: U2.55 (QSPI_SD1), U3.2 (DO(IO1))
/QSPI_SD2: U2.54 (QSPI_SD2), U3.3 (IO2)
/QSPI_SD3: U2.51 (QSPI_SD3), U3.7 (IO3)
/RESCAN_N: R9.2, SW1.1, U2.28 (GPIO17)
/RUN_N: R6.2, R12.2, SW2.1, U2.26 (RUN)
/SWCLK: R5.2, U2.24 (SWCLK)
/SWDIO: R4.2, U2.25 (SWD)
/USB_D+: J1.A6 (D+), J1.B6 (D+), R10.1
/USB_D+I: R10.2, U2.47 (USB_DP)
/USB_D-: J1.A7 (D-), J1.B7 (D-), R11.1
/USB_D-I: R11.2, U2.46 (USB_DM)
/XTAL_IN: C12.2, U2.20 (XIN), Y1.2
/XTAL_OUT: R14.2, U2.21 (XOUT)
/XTAL_OUT_PRE: C13.2, R14.1, Y1.1
A0: U2.15 (GPIO12), U4.23 (A0), U5.23 (A0)
A1: U2.14 (GPIO11), U4.22 (A1), U5.22 (A1)
A2: U2.13 (GPIO10), U4.21 (A2), U5.21 (A2)
A3: U2.12 (GPIO9), U4.20 (A3), U5.20 (A3)
E0N_A: U2.9 (GPIO7), U4.18 (E0N)
E0N_B: U2.11 (GPIO8), U5.18 (E0N)
GND: C1.2, C2.1, C3.2, C4.2, C5.2, C6.2, C7.2, C8.2, C9.2, C10.2, C11.2, C12.1, C13.1, C14.2, C15.2, C16.2, C17.2, J1.A1 (GND), J1.A12 (GND), J1.B1 (GND), J1.B12 (GND), J1.S1 (SHIELD), J2.4, J3.2, J3.3, M1.2, M2.2, M3.2, M4.2, M5.2, M6.2, M7.2, M8.2, M9.2, M10.2, M11.2, M12.2, M13.2, M14.2, M15.2, M16.2, M17.2, M18.2, M19.2, M20.2, R7.2, R8.2, SW1.2, SW2.2, SW3.2, U1.1 (GND), U2.19 (TESTEN), U2.57 (GND), U3.4 (GND), U4.12 (GND), U4.19 (E1N), U5.12 (GND), U5.19 (E1N)
SPI0_RX: M1.3, M2.3, M3.3, M4.3, M5.3, M6.3, M7.3, M8.3, M9.3, M10.3, M11.3, M12.3, M13.3, M14.3, M15.3, M16.3, M17.3, M18.3, M19.3, M20.3, U2.27 (GPIO16)
SPI0_SCLK: M1.4, M2.4, M3.4, M4.4, M5.4, M6.4, M7.4, M8.4, M9.4, M10.4, M11.4, M12.4, M13.4, M14.4, M15.4, M16.4, M17.4, M18.4, M19.4, M20.4, U2.29 (GPIO18)
SPI0_TX: M1.6, M2.6, M3.6, M4.6, M5.6, M6.6, M7.6, M8.6, M9.6, M10.6, M11.6, M12.6, M13.6, M14.6, M15.6, M16.6, M17.6, M18.6, M19.6, M20.6, U2.30 (GPIO19)
VBUS: C1.1, J1.A4 (VBUS), J1.A9 (VBUS), J1.B4 (VBUS), J1.B9 (VBUS), U1.3 (VI)
